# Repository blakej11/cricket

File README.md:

This is the hardware and software source for my [Fire Cricket](https://foo.net/cricket/).

Right now the only thing to look at is the circuit diagrams:

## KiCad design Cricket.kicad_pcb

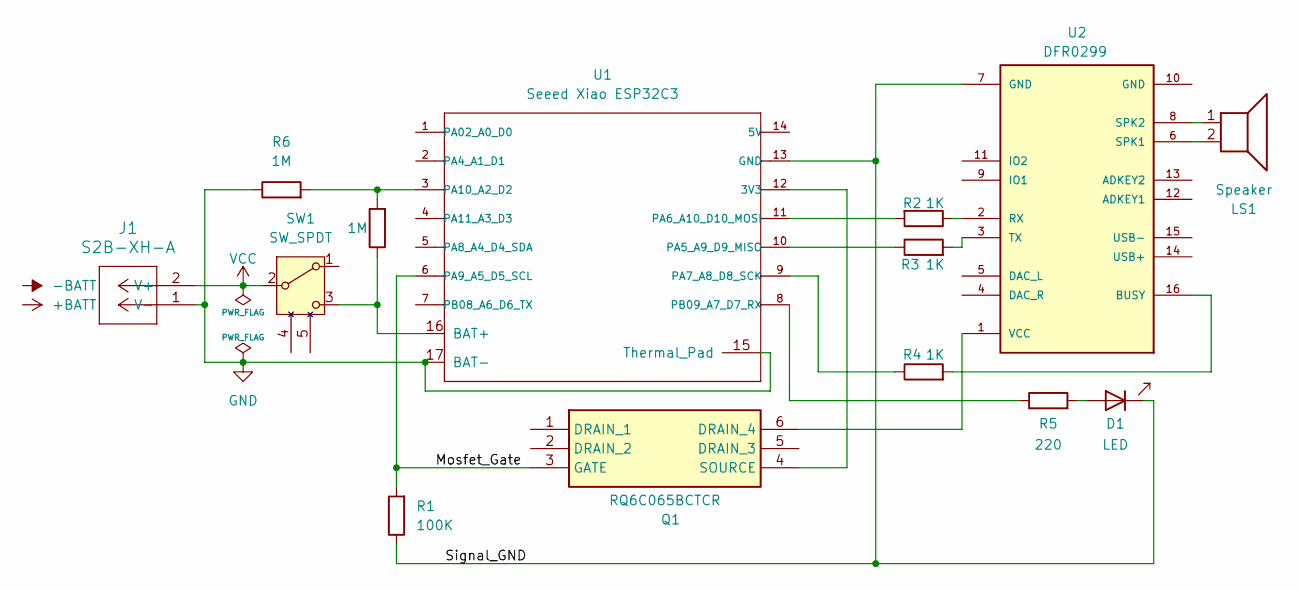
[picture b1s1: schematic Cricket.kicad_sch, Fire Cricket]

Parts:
D1: LED; LED_PLCC_2835_Handsoldering
J1: S2B-XH-A; CONN_S2B-XH-A_JST
LS1: Speaker; Speaker pads
Q1: RQ6C065BCTCR; SOT95P280X100-6N; Mouser Part Number 755-RQ6C065BCTCR
R1: 100K; R_1206_3216Metric_Pad1.30x1.75mm_HandSolder
R2, R3, R4: 1K; R_1206_3216Metric_Pad1.30x1.75mm_HandSolder
R5: 220; R_1206_3216Metric_Pad1.30x1.75mm_HandSolder
R6, R7: 1M; R_1206_3216Metric_Pad1.30x1.75mm_HandSolder
SW1: SW_SPDT; SLW-864574-5A-RA-N-D
U1: Seeed Xiao ESP32C3; MCU_Seeed_ESP32C3
U2: DFR0299; MODULE_DFR0299

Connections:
/Mosfet_Gate: Q1.3 (GATE), R1.2, U1.6 (PA9_A5_D5_SCL)
/Signal_GND: D1.1 (K), R1.1, U1.13 (GND), U2.7 (GND)
GND: J1.1 (V-), R6.1, U1.15 (Thermal_Pad), U1.17 (BAT-)
unnamed: D1.2 (A), R5.2
unnamed: Q1.6 (DRAIN_4), U2.1 (VCC)
unnamed: Q1.4 (SOURCE), U1.12 (3V3)
unnamed: R7.1, SW1.3 (C), U1.16 (BAT+)
unnamed: R3.1, U1.10 (PA5_A9_D9_MISO)
unnamed: R2.2, U1.11 (PA6_A10_D10_MOSI)
unnamed: R4.1, U1.9 (PA7_A8_D8_SCK)
unnamed: R6.2, R7.2, U1.3 (PA10_A2_D2)
unnamed: R5.1, U1.8 (PB09_A7_D7_RX)
unnamed: R4.2, U2.16 (BUSY)
unnamed: R2.1, U2.2 (RX)
unnamed: LS1.2, U2.6 (SPK1)
unnamed: LS1.1, U2.8 (SPK2)
unnamed: R3.2, U2.3 (TX)
VCC: J1.2 (V+), SW1.2 (B)

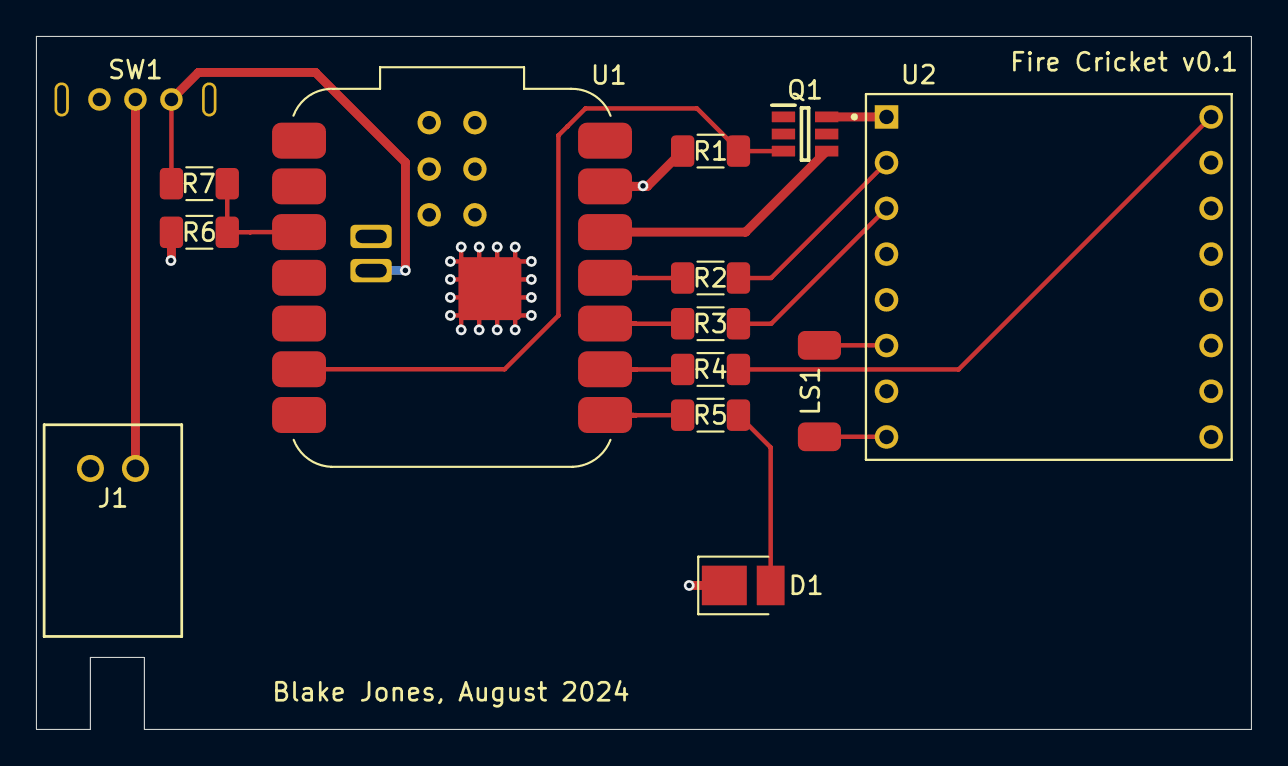
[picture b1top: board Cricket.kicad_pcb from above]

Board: 2 copper layers, 67.5 x 38.5 mm, 14 parts (0 on the bottom side), 18 nets.

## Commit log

2024-08-29 initial revision
2024-08-29 files used for 2024-08-25 board rev
2024-08-29 add images of the circuit board
2024-08-30 move hardware into its own directory
2024-08-30 beginning sketch of a server
2024-08-30 Arduino code to run on the cricket
2024-08-30 need >20 msec delay after commands
2024-08-30 communicate with crickets
2024-08-30 remove old code
2024-09-07 v0.2 tapeout
2024-09-27 Better blink implementation
2024-09-27 Tapeout files for v0.2a
2024-09-27 Hardware for v0.2a (PCBA)
2024-09-27 Revert hardware to v0.2, since I'm using that
2024-09-27 update module path, small tweaks
2024-10-08 use forked zeroconf library
2024-10-08 move simple server aside
2024-10-08 update module name
2024-10-12 new server
2024-10-12 update Go version
2024-10-12 okay try this
2024-10-12 try running it
2024-10-12 try compiling it first
2024-10-12 don't run empty players
2024-10-12 bunch of initial bringup fixes
2024-10-13 more changes
2024-10-13 first sketch of light effects
2024-10-13 refactor
2024-10-13 make more flexible state machine
2024-10-13 blink -> unison
2024-10-13 allow play to specify volume
2024-10-13 move password to separate file
2024-10-14 more
2024-10-14 delay before playing file
2024-10-16 some final tweaks for Autumn Lights
2025-06-22 move to TOML
2025-06-22 some config files
2025-06-22 fix raindrops
2025-07-05 Update the client.Action() API to take a delay rather than an absolute time.
2025-07-05 minor cleanups in play command handling, no semantic change
2025-07-05 update a couple comments
2025-07-06 first cut at storm; updated client interfaces
2025-07-06 another file for individual drips
2025-08-03 Clean up much of last year's (and this year's) tech debt:
    - Effects are now run directly from the lease subsystem,
    and they can accumulate clients over time.
    - The former "client" subsystem is now split out into
    client, device, request, and timedheap.
    - There's now an IDSet type which holds "types.ID"s.
    - Registering effects is cleaner, and uses reflection to fill in
2025-08-10 Fix a couple issues with lease assignment.
    - updateLeasedFraction() was assigning target client counts in the order returned by ws.Slice(), which is ordered by lease weight with possible random shuffling. But increaseFleetSize() was assigning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
    - Now that the lease code is using weights reliably for assigning both fleet fraction and clients, it's clear that the previous "random rotation" algorithm is bogus. That meant that the biggest weigh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
2025-08-15 - fix a bug where a lease holder could have its target client count reduced - better debug logging, especially for leases
2025-08-16 Fix a bug where all sound effects had the same fileset. This happened because they registered a specific instance of their type, so it just got overridden by whatever was registered last.
    To fix this, I "register the type" now, so the effect subsystem can
    instantiate a new instance of it on demand.
2025-08-18 - Allow Shuffle clients to drain independently. This involves some tweaks to IDSet to (a) ensure that it can be closed safely multiple times, (b) ensure that it can handle context cancellation safely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
    - Now that they can drain independently, try harder to pick files that will
    fit in before context expiration.
    - Clean up the Lease state handling, and fix some bugs there.
    - Move playback duration calculation next to the File implementation.
2025-08-20 The new careful selection policy just maximizes the number of reps available. Instead, limit it to the number chosen by the random alg.
2025-08-23 Update many Info logs to be Debug.
2025-08-23 A new storm implementation.
2025-09-22 add support for virtual cricket servers
2025-09-22 add simple builtin virtual cricket server
2025-09-22 parsed the wrong string
2025-09-22 mod tidy
2025-09-22 various config file cleanups
2025-09-22 get storm running with builtinvc
2025-09-22 fix sign of remaining time
2025-09-22 change name of cricket ID parameter
2025-09-23 fix storm intensity scaling; better default storm sounds
